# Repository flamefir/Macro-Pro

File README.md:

# Macro-Pro

## License

**Hardware** (schematics, PCB layout, enclosure/3D files): 
Licensed under [CC BY-NC-SA 4.0](https://creativecommons.org/licenses/by-nc-sa/4.0/).
You are free to build, modify, and share this design for personal and 
non-commercial use, with attribution, under the same license. 
**Commercial sale is not permitted.**

**Firmware**: Based on [QMK](https://github.com/qmk/qmk_firmware), 
licensed under the GNU GPL v2+. The firmware in this repository inherits 
that license. See the firmware directory's LICENSE for details.

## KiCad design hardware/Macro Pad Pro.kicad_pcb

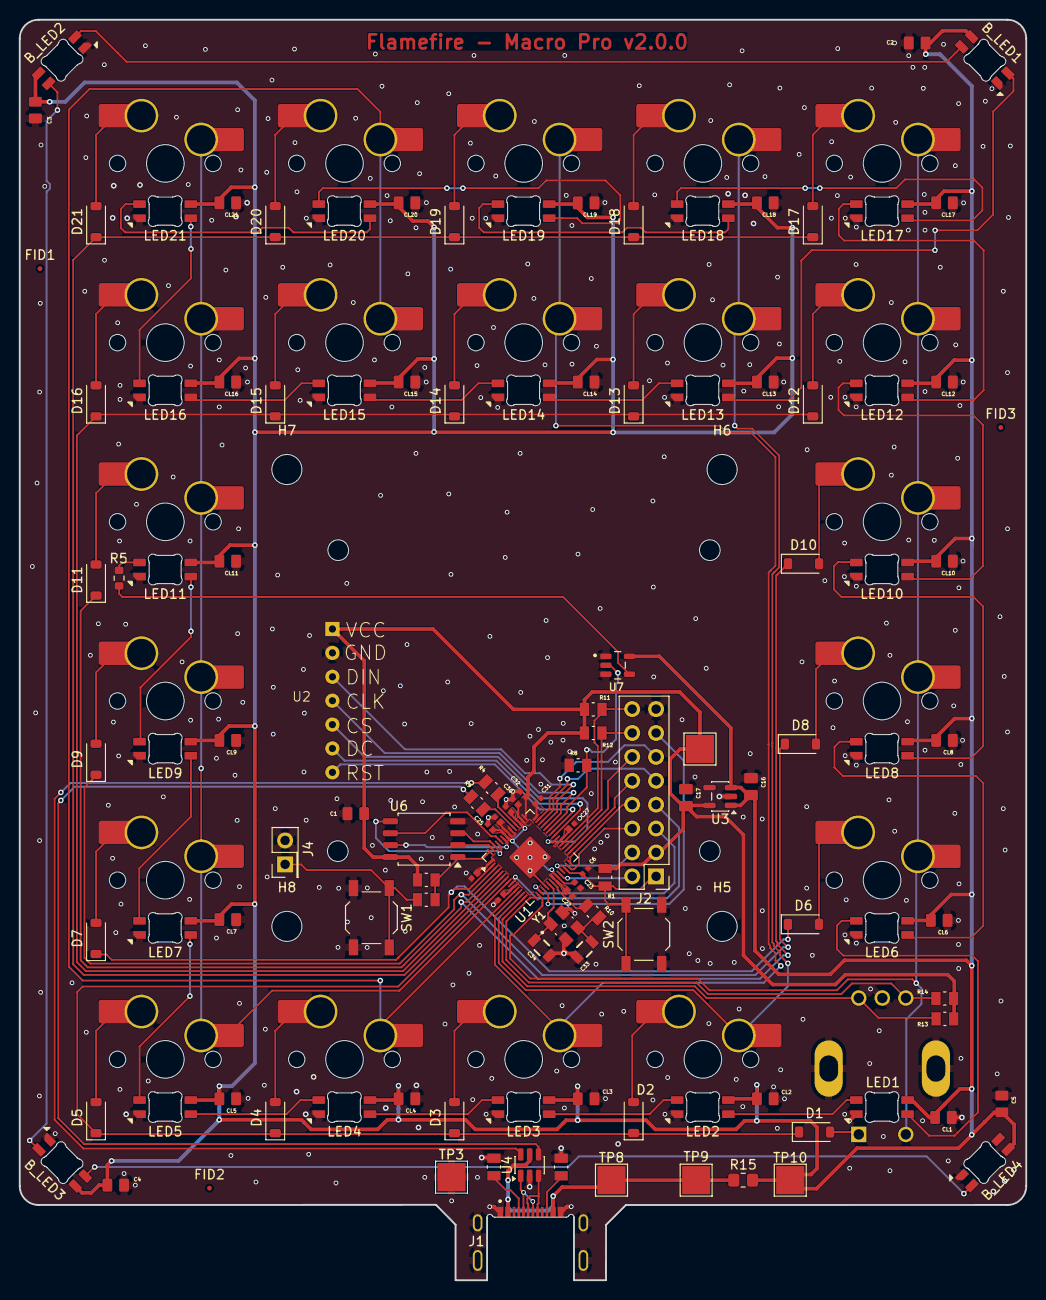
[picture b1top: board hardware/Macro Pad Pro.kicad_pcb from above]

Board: 2 copper layers, 107.0 x 134.0 mm, 148 parts (1 on the bottom side), 103 nets.

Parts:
B_LED1, B_LED2, B_LED3, B_LED4: MX_SK6812MINI-E; LED_MX_6028R_Flipped
C1, C2, C3, C4, C5: 0.1uF; 01uF_0805_CAPC2012X95N
C6, C25, C26, C27, C28, C29, C30, C31, C32, C44: 0.1uF; 01uF_0402_CAPC1005X55N
C16, C17: 10uF; 10uf_0805_CAPC2012X145N
C22, C23: 1uF; 0402_CAPC1005X65N_reduced_pad
C33, C34: 15pF; 15pF_WCAP-CSGP_0805_H0.6_W
CL1, CL2, CL3, CL4, CL5, CL6, CL7, CL8, CL9, CL10, CL11, CL12, CL13, CL14, CL15, CL16, CL17, CL18, CL19, CL20, CL21: 0.1uF; 01uF_0805_CAPC2012X95N
D1, D2, D3, D4, D5, D6, D7, D8, D9, D10, D11, D12, D13, D14, D15, D16, D17, D18, D19, D20, D21: D_SOD-123
FID1, FID2, FID3: Fiducial; Fiducial_0.5mm_Mask1mm
H5, H6, H7, H8: MountingHole; MountingHole_3.2mm_M3
J1: USB_C; USB-C_MOLEX_2169900003
J2: Conn_02x08_Odd_Even; PinHeader_2x08_P2.54mm_Vertical
J4: Conn_02x01; PinHeader_2x01_P2.54mm_Vertical
LED1, LED2, LED3, LED4, LED5, LED6, LED7, LED8, LED9, LED10, LED11, LED12, LED13, LED14, LED15, LED16, LED17, LED18, LED19, LED20, LED21: MX_SK6812MINI-E; LED_MX_6028R
R1, R7, R8, R11, R12, R13, R14: 10k; 10k_RESC2012X65N
R2, R3: 5.1k; 5K1_RESC2012X65N
R4, R9: 27; 27R_RESC2012X65N
R5: 470 ohm; R_0603_1608Metric
R6, R10: 1k; 1k_RESC2012X65N
R15: 0; R_0805_2012Metric_Pad1.20x1.40mm_HandSolder
S1: RotaryEncoder; XDCR_PEC11R-4230F-S0024
S2, S3, S4, S5, S6, S7, S8, S9, S10, S11, S12, S13, S14, S15, S16, S17, S18, S19, S20, S21: MX_Hotswap_1.00u
SW1: SW_Push_B; SW_SPST_TL3342
SW2: SW_Push_R; SW_SPST_TL3342
TP2, TP3, TP8, TP9, TP10: TestPoint; TestPoint_Pad_3.0x3.0mm
U1: RP2040; QFN-56-1EP_7x7mm_P0.4mm_EP3.2x3.2mm
U2: OLED; OLED_SPI_128x128
U3: AP2112K-3.3; SOT-23-5
U4: USBLC6-2SC6; SOT-23-6
U6: W25Q128JVS; SOIC-8_5.3x5.3mm_P1.27mm
U7: SOT95P280X145-5N
Y1: ABM8-272-T3; XTAL_ABM8-272-T3

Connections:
1V1: C23.2, C25.2, C26.2, U1.23 (DVDD), U1.45 (VREG_VOUT), U1.50 (DVDD)
+3.3V: C1.2, C17.2, C22.2, C27.2, C28.2, C29.2, C30.2, C31.2, C32.2, C44.2, J2.3, R1.2, R7.2, R11.2, R12.2, R13.2, R14.2, TP2.1 (1_1), U1.1 (IOVDD), U1.10 (IOVDD), U1.22 (IOVDD), U1.33 (IOVDD), U1.42 (IOVDD), U1.43 (ADC_AVDD), U1.44 (VREG_VIN), U1.48 (USB_VDD), U1.49 (IOVDD), U2.1 (VCC), U3.5 (VOUT), U6.8 (VCC)
+5V: B_LED1.1 (VDD), B_LED2.1 (VDD), B_LED3.1 (VDD), B_LED4.1 (VDD), C2.2, C3.2, C4.2, C5.2, C16.2, CL1.2, CL2.2, CL3.2, CL4.2, CL5.2, CL6.2, CL7.2, CL8.2, CL9.2, CL10.2, CL11.2, CL12.2, CL13.2, CL14.2, CL15.2, CL16.2, CL17.2, CL18.2, CL19.2, CL20.2, CL21.2, LED1.1 (VDD), LED2.1 (VDD), LED3.1 (VDD), LED4.1 (VDD), LED5.1 (VDD), LED6.1 (VDD), LED7.1 (VDD), LED8.1 (VDD), LED9.1 (VDD), LED10.1 (VDD), LED11.1 (VDD), LED12.1 (VDD), LED13.1 (VDD), LED14.1 (VDD), LED15.1 (VDD), LED16.1 (VDD), LED17.1 (VDD), LED18.1 (VDD), LED19.1 (VDD), LED20.1 (VDD), LED21.1 (VDD), R15.2, TP10.1 (1_1), U3.1 (VIN), U3.3 (EN), U7.5 (VCC)
BOOTSEL: J4.1, R6.2, SW1.1
BS_LEDS: B_LED1.3 (DIN), LED13.2 (DOUT)
Col 0: S1.2, S6.1, S8.1, S10.1, S12.1, S17.1, U1.16 (GPIO13)
Col 1: S2.1, S13.1, S18.1, U1.13 (GPIO10)
Col 2: S3.1, S14.1, S19.1, U1.12 (GPIO9)
Col 3: S4.1, S15.1, S20.1, U1.11 (GPIO8)
Col 4: S5.1, S7.1, S9.1, S11.1, S16.1, S21.1, U1.8 (GPIO6)
ESD_DM: R4.2, U4.6
ESD_DP: R9.2, U4.4
GND: B_LED1.4 (VSS), B_LED2.4 (VSS), B_LED3.4 (VSS), B_LED4.4 (VSS), C1.1, C2.1, C3.1, C4.1, C5.1, C6.1, C16.1, C17.1, C22.1, C23.1, C25.1, C26.1, C27.1, C28.1, C29.1, C30.1, C31.1, C32.1, C33.1, C34.1, C44.1, CL1.1, CL2.1, CL3.1, CL4.1, CL5.1, CL6.1, CL7.1, CL8.1, CL9.1, CL10.1, CL11.1, CL12.1, CL13.1, CL14.1, CL15.1, CL16.1, CL17.1, CL18.1, CL19.1, CL20.1, CL21.1, J1.A1_B12 (GND), J1.B1_A12 (GND), J1.S1 (SHIELD), J1.S2 (SHIELD), J1.S3 (SHIELD), J1.S4 (SHIELD), J2.15, J4.2, LED1.4 (VSS), LED2.4 (VSS), LED3.4 (VSS), LED4.4 (VSS), LED5.4 (VSS), LED6.4 (VSS), LED7.4 (VSS), LED8.4 (VSS), LED9.4 (VSS), LED10.4 (VSS), LED11.4 (VSS), LED12.4 (VSS), LED13.4 (VSS), LED14.4 (VSS), LED15.4 (VSS), LED16.4 (VSS), LED17.4 (VSS), LED18.4 (VSS), LED19.4 (VSS), LED20.4 (VSS), LED21.4 (VSS), R2.1, R3.1, R8.1, S1.C (COM), S1.SH1 (SHIELD), S1.SH2 (SHIELD), SW1.2, SW2.2, TP3.1 (1_1), U1.19 (TESTEN), U1.57 (GND), U2.2 (GND), U3.2 (GND), U4.2, U6.4 (GND), U7.1 (~OE), U7.3 (GND), Y1.2 (GND), Y1.4 (GND)
LEDS: R8.2, U1.37 (GPIO25), U7.2 (A)
LEDS_DIN: R5.1, U7.4 (Y)
MCU_DM: R4.1, U1.46 (USB_DM)
MCU_DP: R9.1, U1.47 (USB_DP)
NRST: C6.2, J2.1, R1.1, SW2.1, U1.26 (RUN)
unnamed: B_LED1.2 (DOUT), B_LED2.3 (DIN)
unnamed: B_LED2.2 (DOUT), B_LED3.3 (DIN)
unnamed: B_LED3.2 (DOUT), B_LED4.3 (DIN)
unnamed: C33.2, R10.1, Y1.3
unnamed: D1.2 (A), S1.1
unnamed: D2.2 (A), S2.2
unnamed: D3.2 (A), S3.2
unnamed: D4.2 (A), S4.2
unnamed: D5.2 (A), S5.2
unnamed: D6.2 (A), S6.2
unnamed: D7.2 (A), S7.2
unnamed: D8.2 (A), S8.2
unnamed: D9.2 (A), S9.2
unnamed: D10.2 (A), S10.2
unnamed: D11.2 (A), S11.2
unnamed: D12.2 (A), S12.2
unnamed: D13.2 (A), S13.2
unnamed: D14.2 (A), S14.2
unnamed: D15.2 (A), S15.2
unnamed: D16.2 (A), S16.2
unnamed: D17.2 (A), S17.2
unnamed: D18.2 (A), S18.2
unnamed: D19.2 (A), S19.2
unnamed: D20.2 (A), S20.2
unnamed: D21.2 (A), S21.2
unnamed: J1.A5 (CC1), R2.2
unnamed: J1.B5 (CC2), R3.2
unnamed: LED1.3 (DIN), LED2.2 (DOUT)
unnamed: LED1.2 (DOUT), LED6.3 (DIN)
unnamed: LED2.3 (DIN), LED3.2 (DOUT)
unnamed: LED3.3 (DIN), LED4.2 (DOUT)
unnamed: LED4.3 (DIN), LED5.2 (DOUT)
unnamed: LED5.3 (DIN), LED7.2 (DOUT)
unnamed: LED6.2 (DOUT), LED8.3 (DIN)
unnamed: LED7.3 (DIN), LED9.2 (DOUT)
unnamed: LED8.2 (DOUT), LED10.3 (DIN)
unnamed: LED10.2 (DOUT), LED12.3 (DIN)
unnamed: LED11.3 (DIN), R5.2
unnamed: LED9.3 (DIN), LED11.2 (DOUT)
unnamed: LED12.2 (DOUT), LED17.3 (DIN)
unnamed: LED13.3 (DIN), LED14.2 (DOUT)
unnamed: LED14.3 (DIN), LED15.2 (DOUT)
unnamed: LED15.3 (DIN), LED16.2 (DOUT)
unnamed: LED16.3 (DIN), LED21.2 (DOUT)
unnamed: LED17.2 (DOUT), LED18.3 (DIN)
unnamed: LED18.2 (DOUT), LED19.3 (DIN)
unnamed: LED19.2 (DOUT), LED20.3 (DIN)
unnamed: LED20.2 (DOUT), LED21.3 (DIN)
OLED_CLK: U1.38 (GPIO26/ADC0), U2.4 (CLK)
OLED_CS: U1.34 (GPIO22), U2.5 (CS)
OLED_DC: U1.35 (GPIO23), U2.6 (DC)
OLED_MOSI: U1.39 (GPIO27/ADC1), U2.3 (MOSI/DIN)
OLED_RST: U1.36 (GPIO24), U2.7 (RST)
QSPI_SCLK: U1.52 (QSPI_SCLK), U6.6 (CLK)
QSPI_SD1: U1.55 (QSPI_SD1), U6.2 (DO/IO_{1})
QSPI_SD2: U1.54 (QSPI_SD2), U6.3 (~WP/IO_{2})
QSPI_SD3: U1.51 (QSPI_SD3), U6.7 (~HOLD/~RESET/IO_{3})
QSPI_SDO: U1.53 (QSPI_SD0), U6.5 (DI/IO_{0})
QSPI_SS: R6.1, R7.1, U1.56 (~QSPI_SS), U6.1 (~CS)
RCpinA: R13.1, S1.A, U1.14 (GPIO11)
RCpinB: R14.1, S1.B, U1.15 (GPIO12)
Row 0: D1.1 (K), D2.1 (K), D3.1 (K), D4.1 (K), D5.1 (K), U1.7 (GPIO5)
Row 1: D6.1 (K), D7.1 (K), U1.2 (GPIO0)
Row 2: D8.1 (K), D9.1 (K), U1.3 (GPIO1)
Row 3: D10.1 (K), D11.1 (K), U1.4 (GPIO2)
Row 4: D12.1 (K), D13.1 (K), D14.1 (K), D15.1 (K), D16.1 (K), U1.5 (GPIO3)
Row 5: D17.1 (K), D18.1 (K), D19.1 (K), D20.1 (K), D21.1 (K), U1.6 (GPIO4)
SCL: J2.16, R11.1, U1.32 (GPIO21)
SDA: J2.14, R12.1, U1.31 (GPIO20)
UMP_13: J2.5, U1.17 (GPIO14)
UMP_14: J2.9, U1.40 (GPIO28/ADC2)
UMP_15: J2.7, U1.9 (GPIO7)
UMP_16: J2.6, U1.27 (GPIO16)
UMP_17: J2.10, U1.29 (GPIO18)
UMP_18: J2.12, U1.30 (GPIO19)
UMP_19: J2.8, U1.28 (GPIO17)
UMP_20: J2.11, U1.41 (GPIO29/ADC3)
UMP_21: J2.13, U1.18 (GPIO15)
UMP_SWCLK: J2.2, U1.24 (SWCLK)
UMP_SWDIO: J2.4, U1.25 (SWDIO)
USB_C_DM: J1.A7 (DN1), J1.B7 (DN2), U4.1
USB_C_DP: J1.A6 (DP1), J1.B6 (DP2), U4.3
VBUS: J1.A4_B9 (VBUS), J1.B4_A9 (VBUS), R15.1, TP8.1 (1_1), TP9.1 (1_1), U4.5
XIN: C34.2, U1.20 (XIN), Y1.1
XOUT: R10.2, U1.21 (XOUT)

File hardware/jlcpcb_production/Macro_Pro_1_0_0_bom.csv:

Comment,Designator,Footprint,LCSC Part #
"0.1uF,""C1, C2, C3, C4, C5, CL1, CL10, CL11, CL12, CL13, CL14, CL15, CL16, CL17, CL18, CL19, CL2, CL20, CL21, CL3, CL4, CL5, CL6, CL7, CL8, CL9"",01uF_0805_CAPC2012X95N,C1711"
"10uF,""C16, C17"",10uf_0805_CAPC2012X145N,C15850"
"1uF,""C22, C23"",0402_CAPC1005X65N_reduced_pad,C52923"
"0.1uF,""C25, C26, C27, C28, C29, C30, C31, C32, C44, C6"",01uF_0402_CAPC1005X55N,C1525"
"15pF,""C33, C34"",15pF_WCAP-CSGP_0805_H0.6_W,C107110"
"~,""D1, D10, D11, D12, D13, D14, D15, D16, D17, D18, D19, D2, D20, D21, D3, D4, D5, D6, D7, D8, D9"",D_SOD-123,C917030"
"10k,""R1, R11, R12, R13, R14, R7, R8"",10k_RESC2012X65N,C17414"
"1k,""R10, R6"",1k_RESC2012X65N,C95781"
0,R15,0805,C17477
"5.1k,""R2, R3"",5K1_RESC2012X65N,C27834"
"27,""R4, R9"",27R_RESC2012X65N,C17594"
470 ohm,R5,0603,C23179
SW_Push_B,SW1,SW_SPST_TL3342,C318884
SW_Push_R,SW2,SW_SPST_TL3342,C318884
RP2040,U1,QFN-56-1EP_7x7mm_P0.4mm_EP3.2x3.2mm,C2040
AP2112K-3.3,U3,SOT-23-5,C51118
USBLC6-2SC6,U4,SOT-23-6,C7519
W25Q128JVS,U6,SOIC-8_5.3x5.3mm_P1.27mm,C97521
~,U7,SOT95P280X145-5N,C7484
ABM8-272-T3,Y1,XTAL_ABM8-272-T3,C20625731

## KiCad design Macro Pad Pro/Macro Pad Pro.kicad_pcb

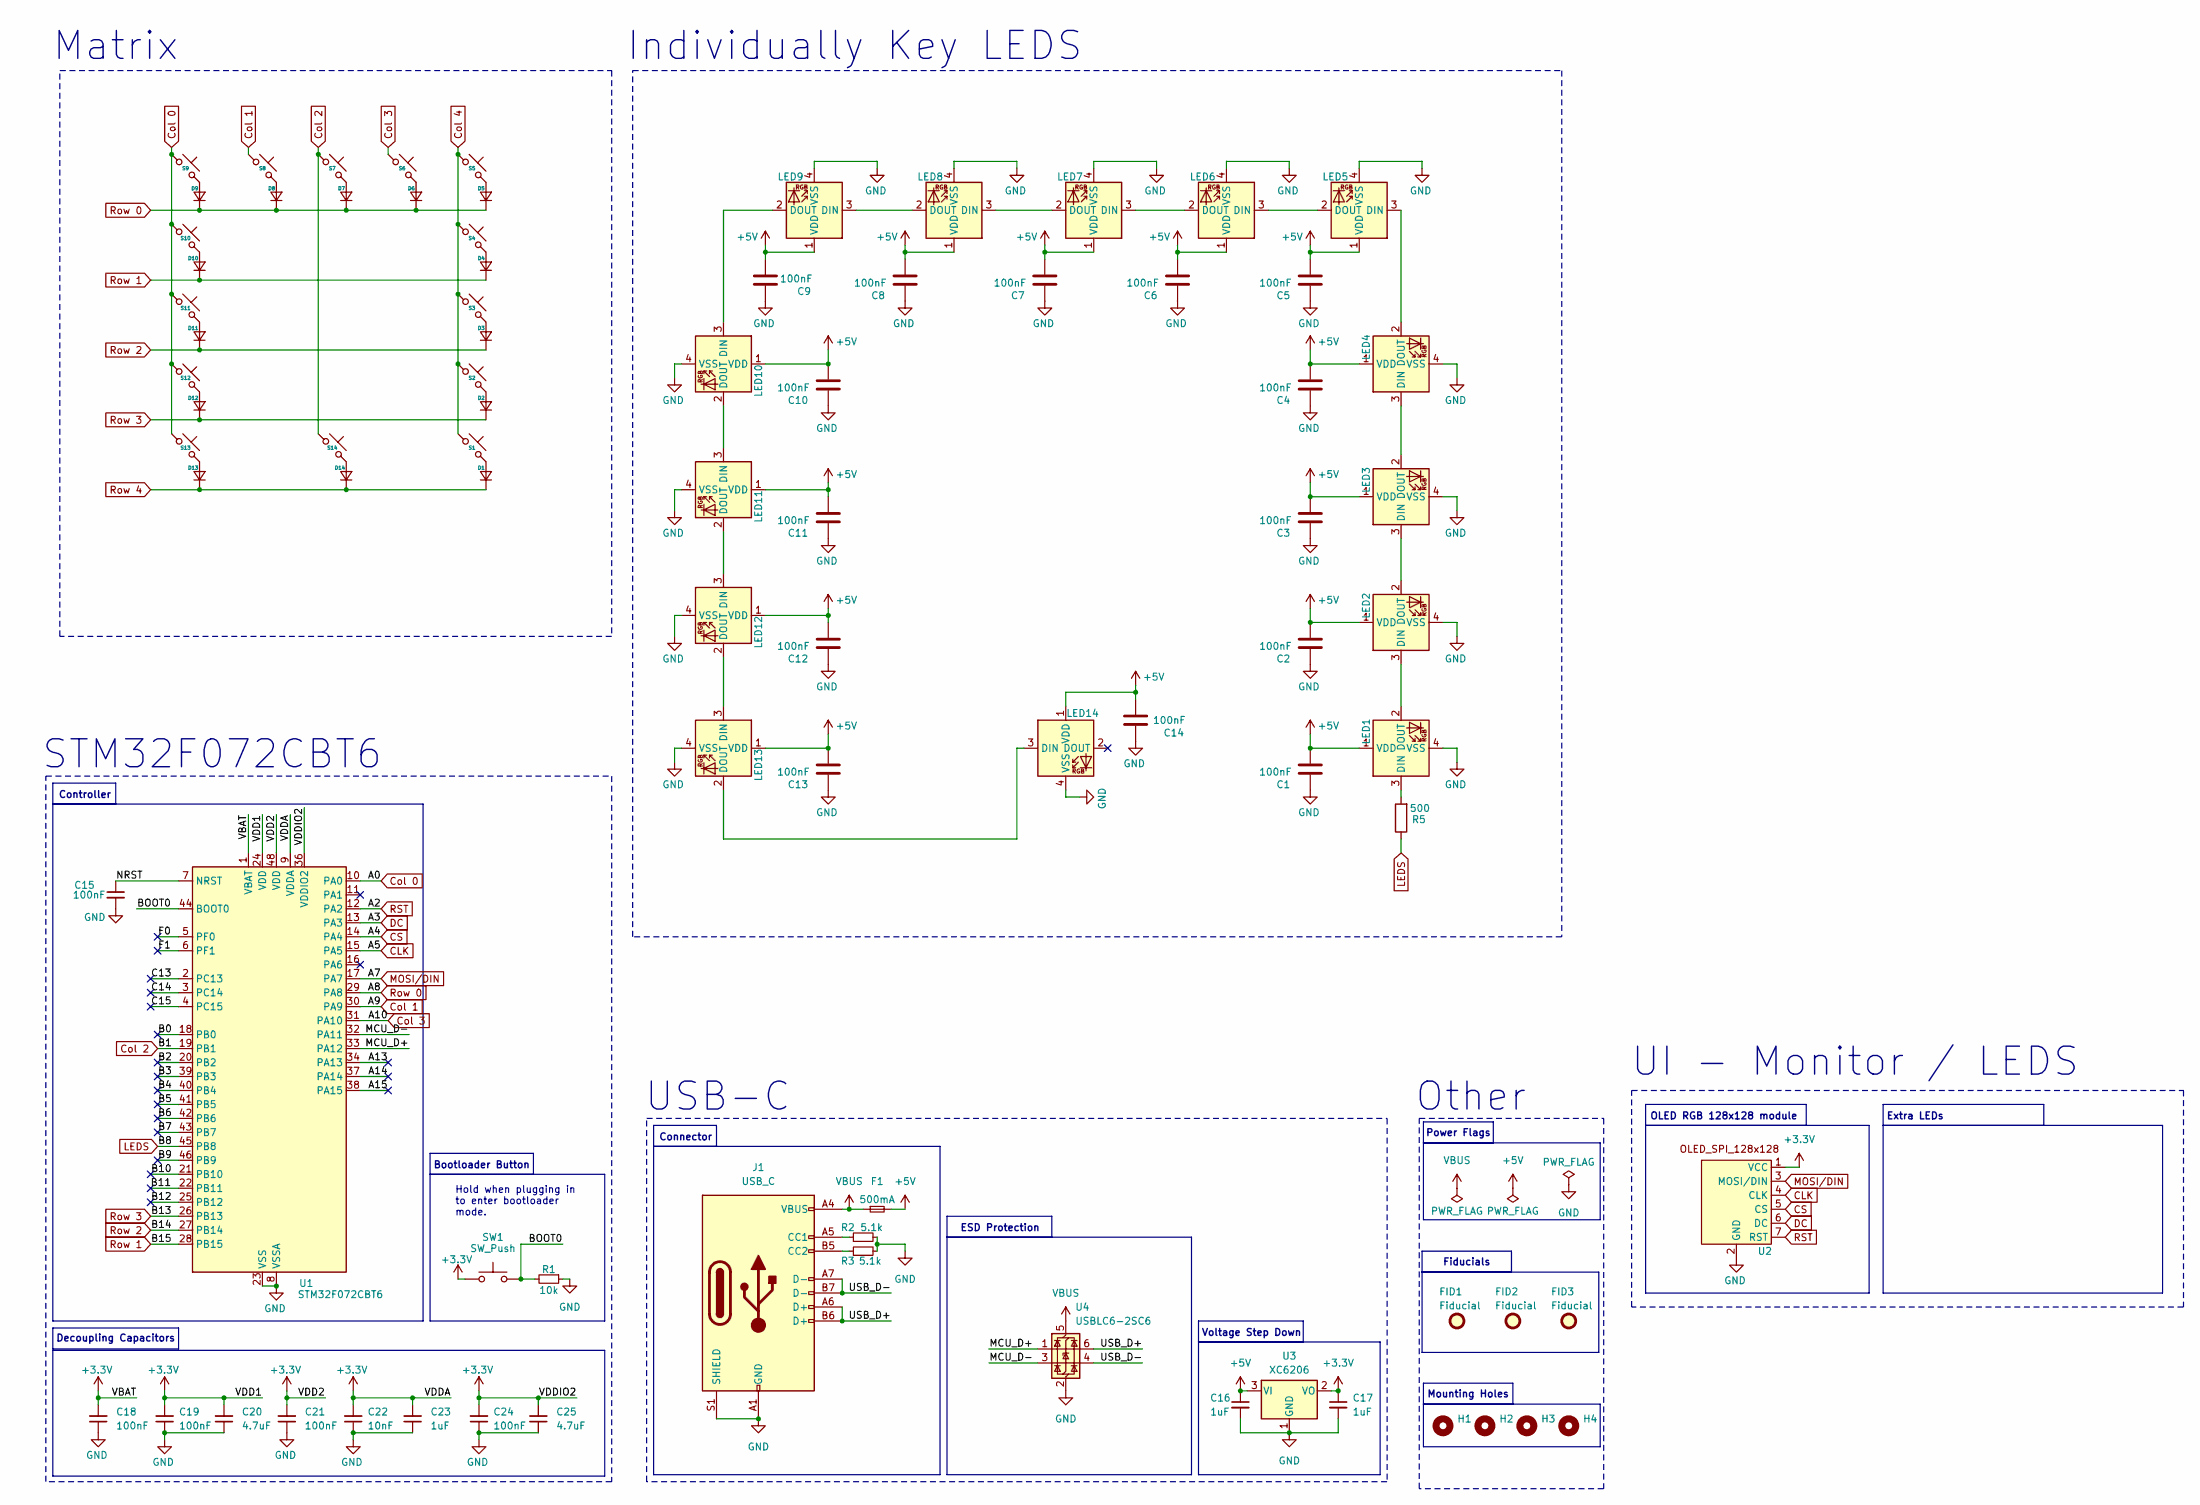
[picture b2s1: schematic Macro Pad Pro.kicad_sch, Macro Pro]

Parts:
C1, C2, C3, C4, C5, C6, C7, C8, C9, C10, C11, C12, C13, C14: 100nF; Capacitor_0603
C15: 100nF; Capacitor_0603; LCSC C307331
C16, C17: 1uF; Capacitor_0603; LCSC C52923
C18, C19, C21, C24: 100nF; Capacitor_0603; MPN CL05B104KB54PNC; LCSC C307331
C20, C25: 4.7uF; Capacitor_0603; MPN CL05A475MP5NRNC; LCSC C23733
C22: 10nF; Capacitor_0603; MPN CL05B103KB5NNNC; LCSC C15195
C23: 1uF; Capacitor_0603; MPN CL05A105KA5NQNC; LCSC C52923
D1, D2, D3, D4, D5, D6, D7, D8, D9, D10, D11, D12, D13, D14: Diode_SOD-123
F1: 500mA; Fuse_0603; LCSC C210357
FID1, FID2, FID3: Fiducial; Fiducial_0.5mm_Mask1mm
H1, H2, H3, H4: MountingHole; MountingHole_3.2mm_M3_DIN965_Pad
J1: USB_C; USB_C_HRO_TYPE-C-31-M-12; LCSC C165948
LED1, LED2, LED3, LED4, LED5, LED6, LED7, LED8, LED9, LED10, LED11, LED12, LED13, LED14: MX_SK6812MINI-E; LED_MX_6028R
R1: 10k; Resistor_0805; LCSC C25744
R2, R3: 5.1k; Resistor_0402; LCSC C25905
R5: 500; R_0603_1608Metric
S1, S2, S3, S4, S5, S6, S7, S8, S9, S10, S11, S12, S13: MX_Hotswap_1.00u
S14: MX_Hotswap_3.00u
SW1: SW_Push; Button_TL3342; LCSC C115351
U1: STM32F072CBT6; Package_LQFP-48_7x7mm_P0.5; LCSC C81720
U2: OLED_SPI_128x128
U3: XC6206; Voltage_SOT-23; LCSC C5446
U4: USBLC6-2SC6; ESD_SOT-23-6; LCSC C2827654

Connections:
+3.3V: C17.1, C18.2, C19.2, C20.2, C21.2, C22.2, C23.2, C24.2, C25.2, SW1.1, U1.1 (VBAT), U1.9 (VDDA), U1.24 (VDD), U1.36 (VDDIO2), U1.48 (VDD), U2.1 (VCC), U3.2 (VO)
+5V: C1.2, C2.2, C3.2, C4.2, C5.2, C6.2, C7.2, C8.2, C9.2, C10.2, C11.2, C12.2, C13.2, C14.2, C16.1, F1.2, LED1.1 (VDD), LED2.1 (VDD), LED3.1 (VDD), LED4.1 (VDD), LED5.1 (VDD), LED6.1 (VDD), LED7.1 (VDD), LED8.1 (VDD), LED9.1 (VDD), LED10.1 (VDD), LED11.1 (VDD), LED12.1 (VDD), LED13.1 (VDD), LED14.1 (VDD), U3.3 (VI)
/A13: U1.34 (PA13)
/A14: U1.37 (PA14)
/A15: U1.38 (PA15)
/B0: U1.18 (PB0)
/B2: U1.20 (PB2)
/B3: U1.39 (PB3)
/B4: U1.40 (PB4)
/B5: U1.41 (PB5)
/B6: U1.42 (PB6)
/B7: U1.43 (PB7)
/B9: U1.46 (PB9)
/B10: U1.21 (PB10)
/B11: U1.22 (PB11)
/B12: U1.25 (PB12)
/BOOT0: R1.2, SW1.2, U1.44 (BOOT0)
/C13: U1.2 (PC13)
/C14: U1.3 (PC14)
/C15: U1.4 (PC15)
/F0: U1.5 (PF0)
/F1: U1.6 (PF1)
/MCU_D+: U1.33 (PA12), U4.1 (I/O1)
/MCU_D-: U1.32 (PA11), U4.3 (I/O2)
/NRST: C15.1, U1.7 (NRST)
/USB_D+: J1.A6 (D+), J1.B6 (D+), U4.6 (I/O1)
/USB_D-: J1.A7 (D-), J1.B7 (D-), U4.4 (I/O2)
CLK: U1.15 (PA5), U2.4 (CLK)
CS: U1.14 (PA4), U2.5 (CS)
Col 0: S9.1, S10.1, S11.1, S12.1, S13.1, U1.10 (PA0)
Col 1: S8.1, U1.30 (PA9)
Col 2: S7.1, S14.1, U1.19 (PB1)
Col 3: S6.1, U1.31 (PA10)
Col 4: S1.1, S2.1, S3.1, S4.1, S5.1
DC: U1.13 (PA3), U2.6 (DC)
GND: C1.1, C2.1, C3.1, C4.1, C5.1, C6.1, C7.1, C8.1, C9.1, C10.1, C11.1, C12.1, C13.1, C14.1, C15.2, C16.2, C17.2, C18.1, C19.1, C20.1, C21.1, C22.1, C23.1, C24.1, C25.1, J1.A1 (GND), J1.A12 (GND), J1.B1 (GND), J1.B12 (GND), J1.S1 (SHIELD), LED1.4 (VSS), LED2.4 (VSS), LED3.4 (VSS), LED4.4 (VSS), LED5.4 (VSS), LED6.4 (VSS), LED7.4 (VSS), LED8.4 (VSS), LED9.4 (VSS), LED10.4 (VSS), LED11.4 (VSS), LED12.4 (VSS), LED13.4 (VSS), LED14.4 (VSS), R1.1, R2.2, R3.2, U1.8 (VSSA), U1.23 (VSS), U1.35 (VSS), U1.47 (VSS), U2.2 (GND), U3.1 (GND), U4.2 (GND)
LEDS: R5.1, U1.45 (PB8)
MOSI/DIN: U1.17 (PA7), U2.3 (MOSI/DIN)
unnamed: D1.2 (A), S1.2
unnamed: D2.2 (A), S2.2
unnamed: D3.2 (A), S3.2
unnamed: D4.2 (A), S4.2
unnamed: D5.2 (A), S5.2
unnamed: D6.2 (A), S6.2
unnamed: D7.2 (A), S7.2
unnamed: D8.2 (A), S8.2
unnamed: D9.2 (A), S9.2
unnamed: D10.2 (A), S10.2
unnamed: D11.2 (A), S11.2
unnamed: D12.2 (A), S12.2
unnamed: D13.2 (A), S13.2
unnamed: D14.2 (A), S14.2
unnamed: J1.A5 (CC1), R2.1
unnamed: J1.B5 (CC2), R3.1
unnamed: LED1.3 (DIN), R5.2
unnamed: LED1.2 (DOUT), LED2.3 (DIN)
unnamed: LED2.2 (DOUT), LED3.3 (DIN)
unnamed: LED3.2 (DOUT), LED4.3 (DIN)
unnamed: LED4.2 (DOUT), LED5.3 (DIN)
unnamed: LED5.2 (DOUT), LED6.3 (DIN)
unnamed: LED6.2 (DOUT), LED7.3 (DIN)
unnamed: LED7.2 (DOUT), LED8.3 (DIN)
unnamed: LED8.2 (DOUT), LED9.3 (DIN)
unnamed: LED9.2 (DOUT), LED10.3 (DIN)
unnamed: LED10.2 (DOUT), LED11.3 (DIN)
unnamed: LED11.2 (DOUT), LED12.3 (DIN)
unnamed: LED12.2 (DOUT), LED13.3 (DIN)
unnamed: LED13.2 (DOUT), LED14.3 (DIN)
RST: U1.12 (PA2), U2.7 (RST)
Row 0: D5.1 (K), D6.1 (K), D7.1 (K), D8.1 (K), D9.1 (K), U1.29 (PA8)
Row 1: D4.1 (K), D10.1 (K), U1.28 (PB15)
Row 2: D3.1 (K), D11.1 (K), U1.27 (PB14)
Row 3: D2.1 (K), D12.1 (K), U1.26 (PB13)
Row 4: D1.1 (K), D13.1 (K), D14.1 (K)
VBUS: F1.1, J1.A4 (VBUS), J1.A9 (VBUS), J1.B4 (VBUS), J1.B9 (VBUS), U4.5 (VBUS)

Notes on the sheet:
STM32F072CBT6
UI - Monitor / LEDS
USB-C
Mounting Holes
Individually Key LEDS
Fiducials
Decoupling Capacitors
Controller
ESD Protection
Power Flags
OLED RGB 128x128 module
Voltage Step Down
Extra LEDs
Other
Bootloader Button
Matrix
Connector
Hold when plugging in to enter bootloader mode.

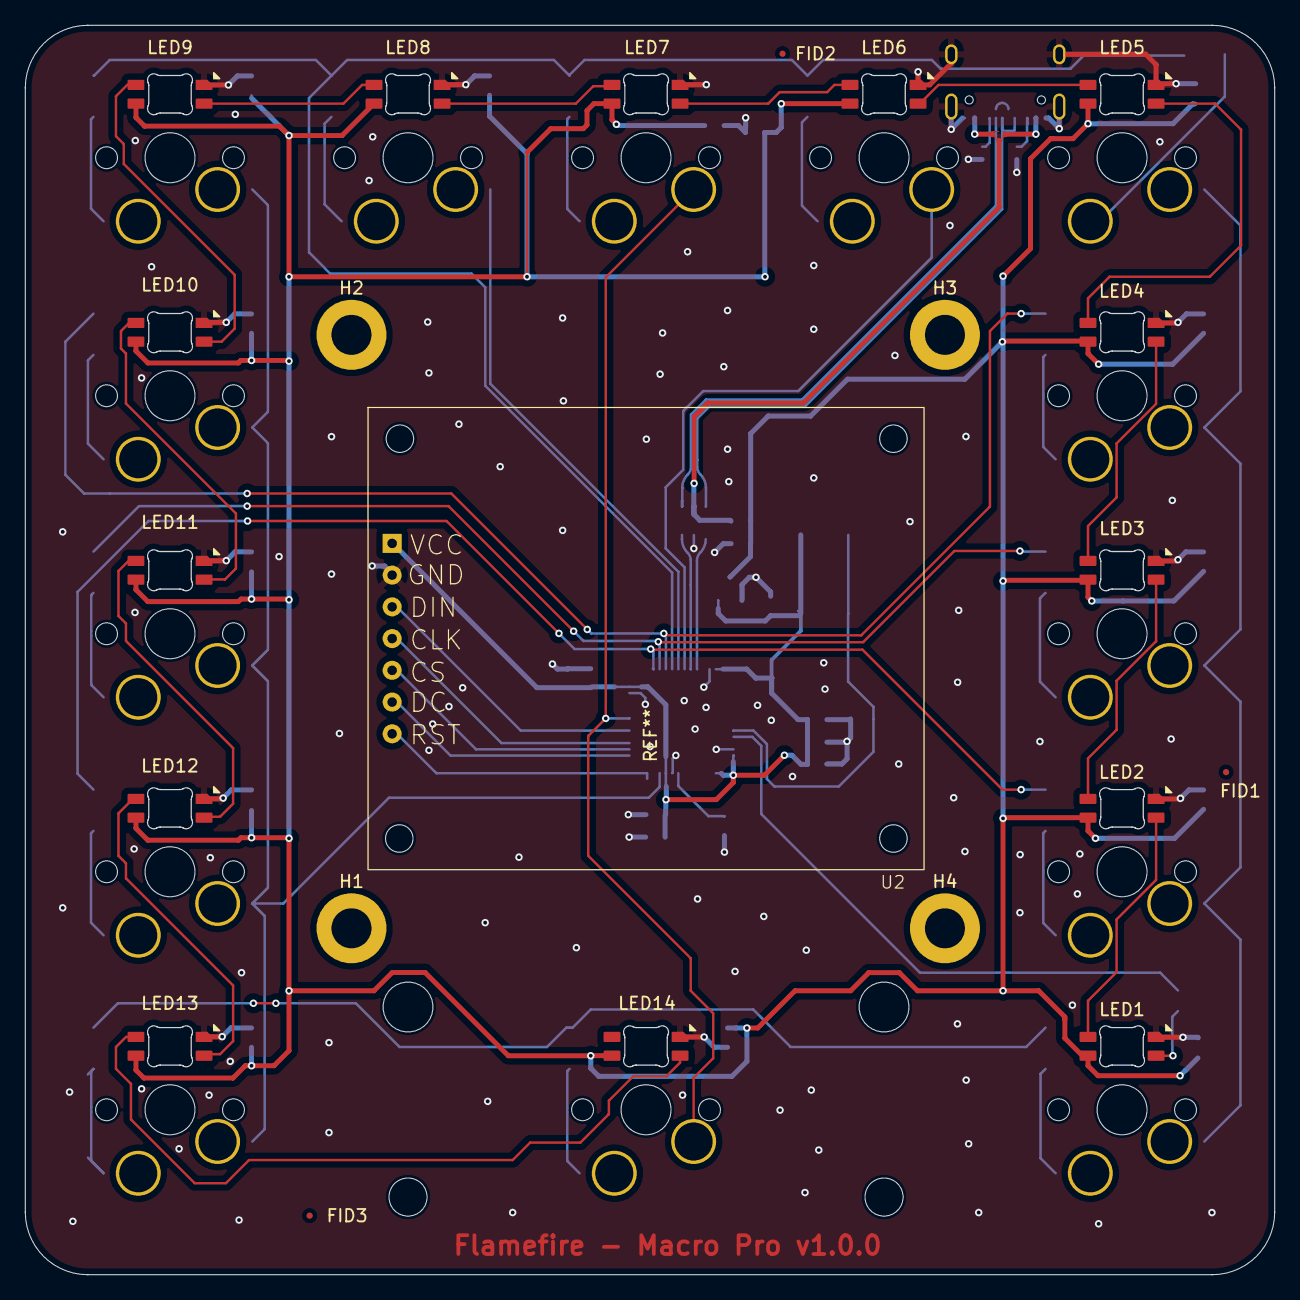
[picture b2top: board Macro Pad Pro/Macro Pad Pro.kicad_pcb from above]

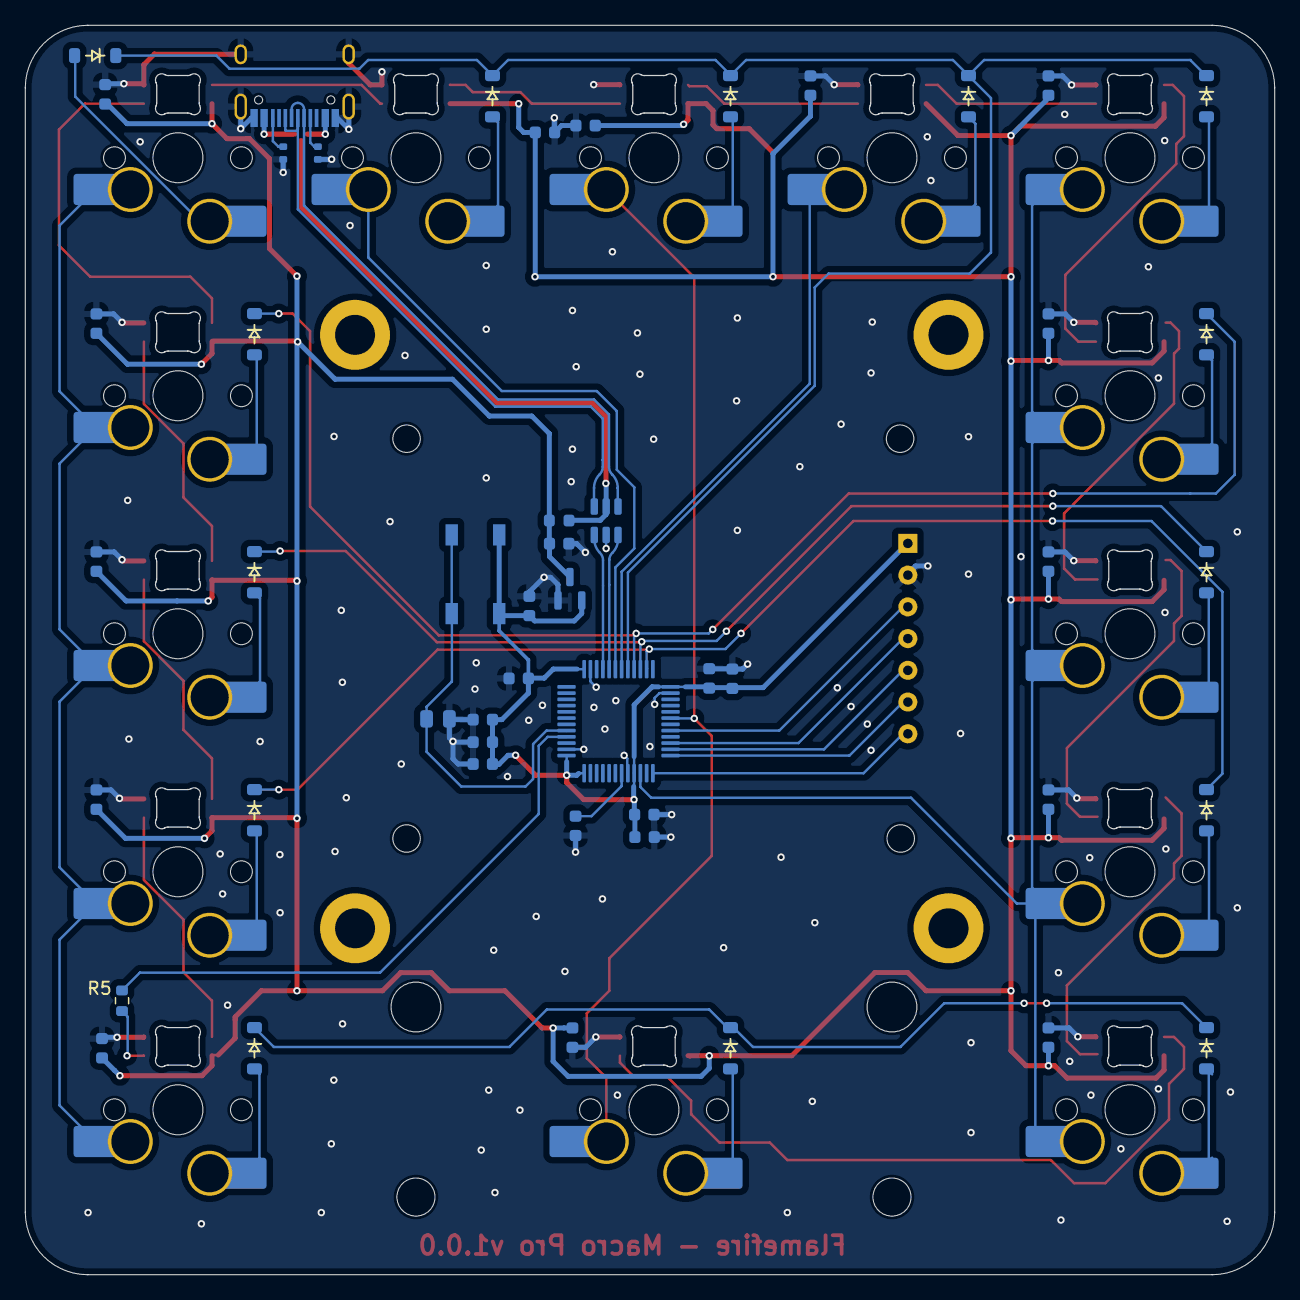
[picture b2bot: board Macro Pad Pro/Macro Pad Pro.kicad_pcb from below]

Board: 4 copper layers, 100.0 x 100.0 mm, 85 parts (63 on the bottom side), 56 nets.

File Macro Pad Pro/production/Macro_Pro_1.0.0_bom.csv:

Designator,Footprint,Quantity,Value,LCSC Part #
"C1, C10, C11, C12, C13, C14, C2, C3, C4, C5, C6, C7, C8, C9",Capacitor_0603,14,100nF,
"C15, C18, C19, C21, C24",Capacitor_0603,5,100nF,C307331
"C16, C17, C23",Capacitor_0603,3,1uF,C52923
"C20, C25",Capacitor_0603,2,4.7uF,C23733
C22,Capacitor_0603,1,10nF,C15195
"D1, D10, D11, D12, D13, D14, D2, D3, D4, D5, D6, D7, D8, D9",Diode_SOD-123,14,~,
F1,Fuse_0603,1,500mA,C210357
J1,USB_C_HRO_TYPE-C-31-M-12,1,USB_C,C165948
"LED1, LED10, LED11, LED12, LED13, LED14, LED2, LED3, LED4, LED5, LED6, LED7, LED8, LED9",LED_MX_6028R,14,MX_SK6812MINI-E,
R1,Resistor_0805,1,10k,C25744
"R2, R3",Resistor_0402,2,5.1k,C25905
R5,0603,1,500,
"S1, S10, S11, S12, S13, S2, S3, S4, S5, S6, S7, S8, S9",MX_Hotswap_1.00u,13,~,
S14,MX_Hotswap_3.00u,1,~,
SW1,Button_TL3342,1,SW_Push,C115351
U1,Package_LQFP-48_7x7mm_P0.5,1,STM32F072CBT6,C81720
U2,OLED_SPI_128x128,1,~,
U3,Voltage_SOT-23,1,XC6206,C5446
U4,ESD_SOT-23-6,1,USBLC6-2SC6,C2827654

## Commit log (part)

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2026-02-25 First upload of project
2026-05-23 Finished PCB, TODO finish the DRC warnings n stuff and send to review
2026-06-01 from work pc
2026-06-01 added git ignore
2026-06-01 more ignore
2026-06-01 remove .history
2026-06-01 remove backups
2026-06-15 Changes ready for review
2026-06-15 Updated the datalines routing, to be more simple, but longer
2026-06-16 added some design files for making a plate
2026-06-21 cleaned up BOM and updated most components with LCSC number and MPN, sent to PCBWay for review
2026-06-21 Added license files
2026-06-23 Fixed ERC component footprint
2026-06-25 Remove enclosure — moved to Macro-Pro-Enclosure repo

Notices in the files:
README.md:
License: CC BY-NC-SA 4.0
